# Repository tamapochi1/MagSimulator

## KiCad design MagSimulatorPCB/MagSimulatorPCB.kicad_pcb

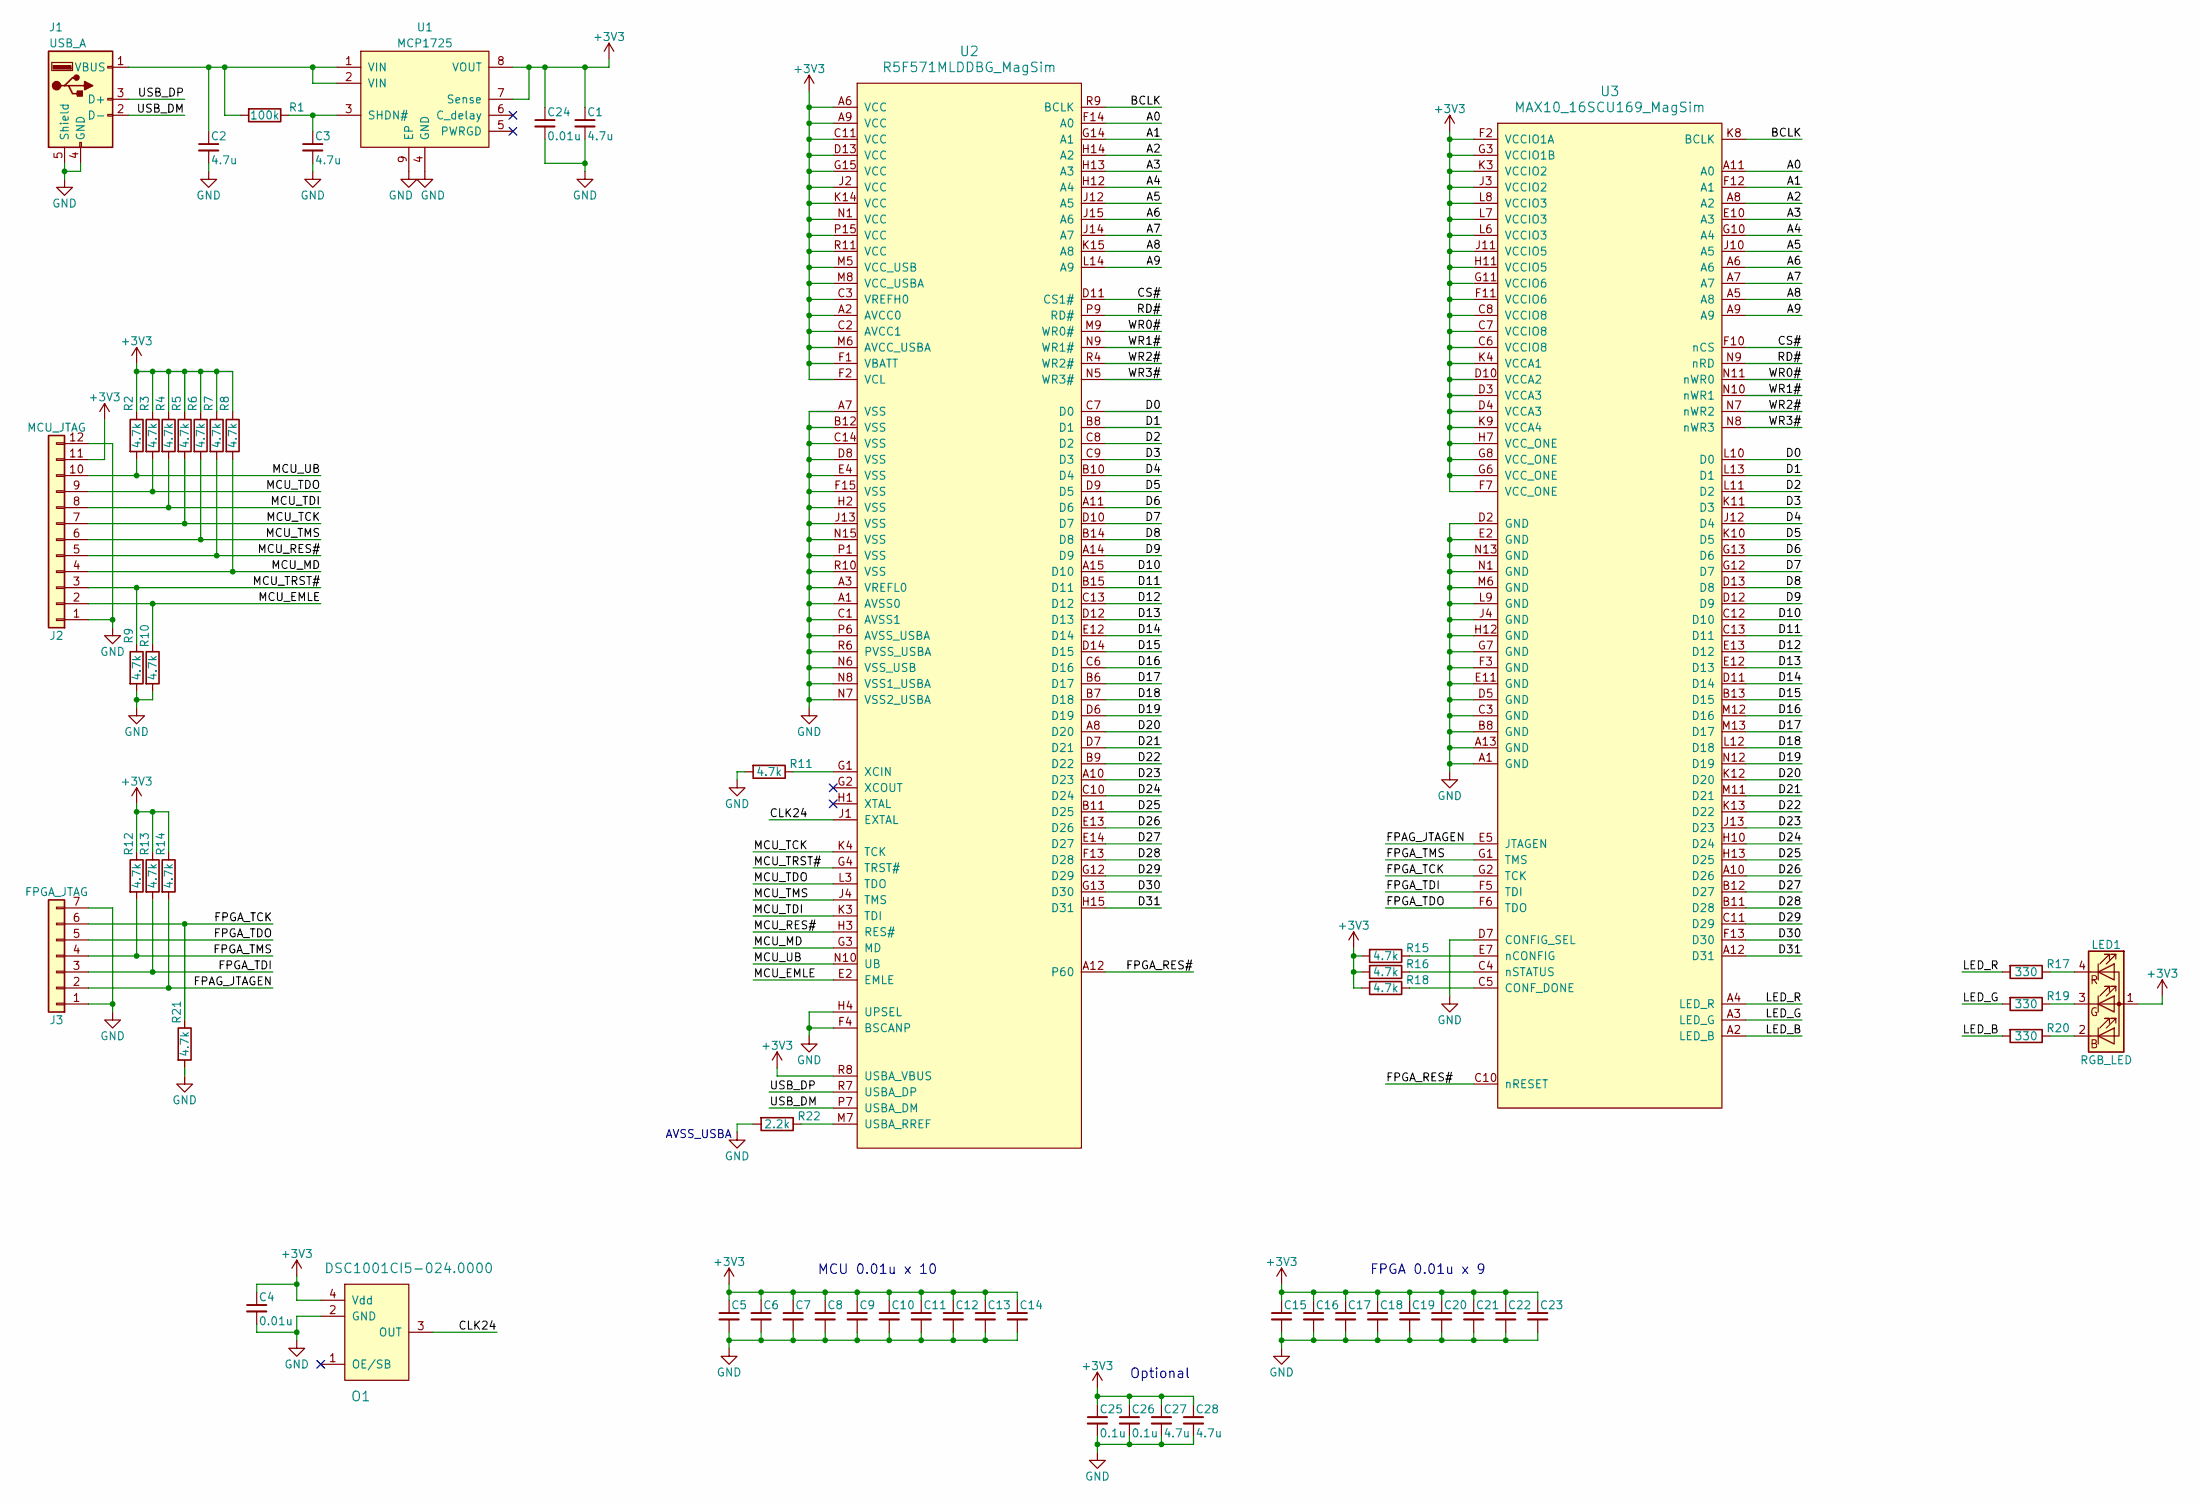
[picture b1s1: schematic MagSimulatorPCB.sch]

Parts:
C1, C2, C3, C27, C28: 4.7u; C_0402_NoSilk
C4, C5, C6, C7, C8, C9, C10, C11, C12, C13, C14, C15, C16, C17, C18, C19, C20, C21, C22, C23, C24: 0.01u; C_0402_NoSilk
C25, C26: 0.1u; C_0402_NoSilk
J1: USB_A; UP2-AH-TH
J2: MCU_JTAG; Pin_Header_Straight_1x12_Pitch1.27mm
J3: FPGA_JTAG; Pin_Header_Straight_1x07_Pitch1.27mm
LED1: RGB_LED; LED_Cree-PLCC4_2x2mm_CW
O1: DSC1001CI5-024.0000; DSC1001_CDFN-4_3.2x2.5
R1: 100k; R_0402_NoSilk
R2, R3, R4, R5, R6, R7, R8, R9, R10, R11, R12, R13, R14, R15, R16, R18, R21: 4.7k; R_0402_NoSilk
R17, R19, R20: 330; R_0402_NoSilk
R22: 2.2k; R_0402_NoSilk
U1: MCP1725; DFN-8-1EP_3x2mm_Pitch0.5mm
U2: R5F571MLDDBG_MagSim; LFBGA_176
U3: MAX10_16SCU169_MagSim; UBGA-169_A_1.55

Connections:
+3V3: C1.1, C4.1, C5.1, C6.1, C7.1, C8.1, C9.1, C10.1, C11.1, C12.1, C13.1, C14.1, C15.1, C16.1, C17.1, C18.1, C19.1, C20.1, C21.1, C22.1, C23.1, C24.1, C25.1, C26.1, C27.1, C28.1, J2.11, LED1.1 (A), O1.4 (Vdd), R2.1, R3.1, R4.1, R5.1, R6.1, R7.1, R8.1, R12.1, R13.1, R14.1, R15.2, R16.2, R18.2, U1.7 (Sense), U1.8 (VOUT), U2.A2 (AVCC0), U2.A6 (VCC), U2.A9 (VCC), U2.C2 (AVCC1), U2.C3 (VREFH0), U2.C11 (VCC), U2.D13 (VCC), U2.F1 (VBATT), U2.F2 (VCL), U2.G15 (VCC), U2.J2 (VCC), U2.K14 (VCC), U2.M5 (VCC_USB), U2.M6 (AVCC_USBA), U2.M8 (VCC_USBA), U2.N1 (VCC), U2.P15 (VCC), U2.R8 (USBA_VBUS), U2.R11 (VCC), U3.C6 (VCCIO8), U3.C7 (VCCIO8), U3.C8 (VCCIO8), U3.D3 (VCCA3), U3.D4 (VCCA3), U3.D10 (VCCA2), U3.F2 (VCCIO1A), U3.F7 (VCC_ONE), U3.F11 (VCCIO6), U3.G3 (VCCIO1B), U3.G6 (VCC_ONE), U3.G8 (VCC_ONE), U3.G11 (VCCIO6), U3.H7 (VCC_ONE), U3.H11 (VCCIO5), U3.J3 (VCCIO2), U3.J11 (VCCIO5), U3.K3 (VCCIO2), U3.K4 (VCCA1), U3.K9 (VCCA4), U3.L6 (VCCIO3), U3.L7 (VCCIO3), U3.L8 (VCCIO3)
/A0: U2.F14 (A0), U3.A11 (A0)
/A1: U2.G14 (A1), U3.F12 (A1)
/A2: U2.H14 (A2), U3.A8 (A2)
/A3: U2.H13 (A3), U3.E10 (A3)
/A4: U2.H12 (A4), U3.G10 (A4)
/A5: U2.J12 (A5), U3.J10 (A5)
/A6: U2.J15 (A6), U3.A6
/A7: U2.J14 (A7), U3.A7
/A8: U2.K15 (A8), U3.A5 (A8)
/A9: U2.L14 (A9), U3.A9
/BCLK: U2.R9 (BCLK), U3.K8 (BCLK)
/CLK24: O1.3 (OUT), U2.J1 (EXTAL)
/CS#: U2.D11 (CS1#), U3.F10 (nCS)
/D0: U2.C7 (D0), U3.L10 (D0)
/D1: U2.B8 (D1), U3.L13 (D1)
/D2: U2.C8 (D2), U3.L11 (D2)
/D3: U2.C9 (D3), U3.K11 (D3)
/D4: U2.B10 (D4), U3.J12 (D4)
/D5: U2.D9 (D5), U3.K10 (D5)
/D6: U2.A11 (D6), U3.G13 (D6)
/D7: U2.D10 (D7), U3.G12 (D7)
/D8: U2.B14 (D8), U3.D13 (D8)
/D9: U2.A14 (D9), U3.D12 (D9)
/D10: U2.A15 (D10), U3.C12 (D10)
/D11: U2.B15 (D11), U3.C13 (D11)
/D12: U2.C13 (D12), U3.E13 (D12)
/D13: U2.D12 (D13), U3.E12 (D13)
/D14: U2.E12 (D14), U3.D11 (D14)
/D15: U2.D14 (D15), U3.B13 (D15)
/D16: U2.C6 (D16), U3.M12 (D16)
/D17: U2.B6 (D17), U3.M13 (D17)
/D18: U2.B7 (D18), U3.L12 (D18)
/D19: U2.D6 (D19), U3.N12 (D19)
/D20: U2.A8 (D20), U3.K12 (D20)
/D21: U2.D7 (D21), U3.M11 (D21)
/D22: U2.B9 (D22), U3.K13 (D22)
/D23: U2.A10 (D23), U3.J13 (D23)
/D24: U2.C10 (D24), U3.H10 (D24)
/D25: U2.B11 (D25), U3.H13 (D25)
/D26: U2.E13 (D26), U3.A10 (D26)
/D27: U2.E14 (D27), U3.B12 (D27)
/D28: U2.F13 (D28), U3.B11 (D28)
/D29: U2.G12 (D29), U3.C11 (D29)
/D30: U2.G13 (D30), U3.F13 (D30)
/D31: U2.H15 (D31), U3.A12 (D31)
/FPAG_JTAGEN: J3.2, R14.2, U3.E5 (JTAGEN)
/FPGA_RES#: U2.A12 (P60), U3.C10 (nRESET)
/FPGA_TCK: J3.6, R21.1, U3.G2 (TCK)
/FPGA_TDI: J3.3, R13.2, U3.F5 (TDI)
/FPGA_TDO: J3.5, U3.F6 (TDO)
/FPGA_TMS: J3.4, R12.2, U3.G1 (TMS)
/LED_B: R20.2, U3.A2 (LED_B)
/LED_G: R19.2, U3.A3 (LED_G)
/LED_R: R17.2, U3.A4 (LED_R)
/MCU_EMLE: J2.2, R10.1, U2.E2 (EMLE)
/MCU_MD: J2.4, R8.2, U2.G3 (MD)
/MCU_RES#: J2.5, R7.2, U2.H3 (RES#)
/MCU_TCK: J2.7, R5.2, U2.K4 (TCK)
/MCU_TDI: J2.8, R4.2, U2.K3 (TDI)
/MCU_TDO: J2.9, R3.2, U2.L3 (TDO)
/MCU_TMS: J2.6, R6.2, U2.J4 (TMS)
/MCU_TRST#: J2.3, R9.1, U2.G4 (TRST#)
/MCU_UB: J2.10, R2.2, U2.N10 (UB)
/RD#: U2.P9 (RD#), U3.N9 (nRD)
/USB_DM: J1.2 (D-), U2.P7 (USBA_DM)
/USB_DP: J1.3 (D+), U2.R7 (USBA_DP)
/WR0#: U2.M9 (WR0#), U3.N11 (nWR0)
/WR1#: U2.N9 (WR1#), U3.N10 (nWR1)
/WR2#: U2.R4 (WR2#), U3.N7 (nWR2)
/WR3#: U2.N5 (WR3#), U3.N8 (nWR3)
GND: C1.2, C2.2, C3.2, C4.2, C5.2, C6.2, C7.2, C8.2, C9.2, C10.2, C11.2, C12.2, C13.2, C14.2, C15.2, C16.2, C17.2, C18.2, C19.2, C20.2, C21.2, C22.2, C23.2, C24.2, C25.2, C26.2, C27.2, C28.2, J1.4 (GND), J1.5 (Shield), J2.1, J2.12, J3.1, J3.7, O1.2 (GND), R9.2, R10.2, R11.2, R21.2, R22.2, U1.4 (GND), U1.9 (EP), U2.A1 (AVSS0), U2.A3 (VREFL0), U2.A7 (VSS), U2.B12 (VSS), U2.C1 (AVSS1), U2.C14 (VSS), U2.D8 (VSS), U2.E4 (VSS), U2.F4 (BSCANP), U2.F15 (VSS), U2.H2 (VSS), U2.H4 (UPSEL), U2.J13 (VSS), U2.N6 (VSS_USB), U2.N7 (VSS2_USBA), U2.N8 (VSS1_USBA), U2.N15 (VSS), U2.P1 (VSS), U2.P6 (AVSS_USBA), U2.R6 (PVSS_USBA), U2.R10 (VSS), U3.A1 (GND), U3.A13 (GND), U3.B8 (GND), U3.C3 (GND), U3.D2 (GND), U3.D5 (GND), U3.D7 (CONFIG_SEL), U3.E2 (GND), U3.E11 (GND), U3.F3 (GND), U3.G7 (GND), U3.H12 (GND), U3.J4 (GND), U3.L9 (GND), U3.M6 (GND), U3.N1 (GND), U3.N13 (GND)
unnamed: C2.1, J1.1 (VBUS), R1.2, U1.1 (VIN), U1.2 (VIN)
unnamed: C3.1, R1.1, U1.3 (SHDN#)
unnamed: LED1.2 (BK), R20.1
unnamed: LED1.3 (GK), R19.1
unnamed: LED1.4 (RK), R17.1
unnamed: R11.1, U2.G1 (XCIN)
unnamed: R15.1, U3.E7 (nCONFIG)
unnamed: R16.1, U3.C4 (nSTATUS)
unnamed: R18.1, U3.C5 (CONF_DONE)
unnamed: R22.1, U2.M7 (USBA_RREF)

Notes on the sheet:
AVSS_USBA
MCU 0.01u x 10
FPGA 0.01u x 9
Optional

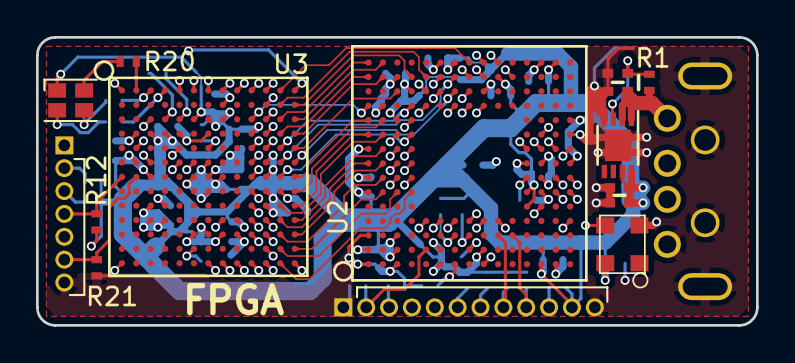
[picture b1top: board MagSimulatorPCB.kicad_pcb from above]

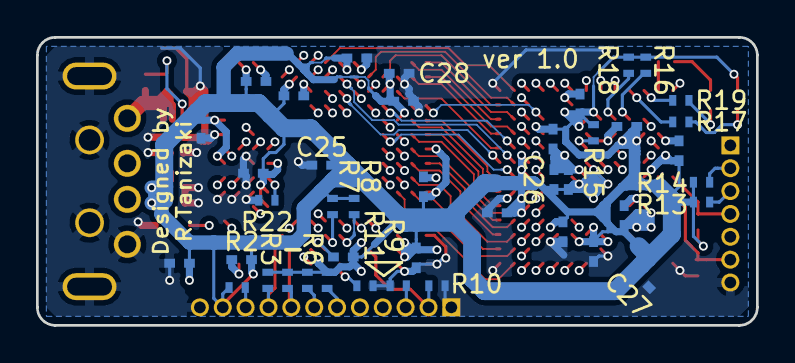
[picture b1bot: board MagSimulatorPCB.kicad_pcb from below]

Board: 4 copper layers, 40.0 x 16.0 mm, 58 parts (42 on the bottom side), 82 nets.

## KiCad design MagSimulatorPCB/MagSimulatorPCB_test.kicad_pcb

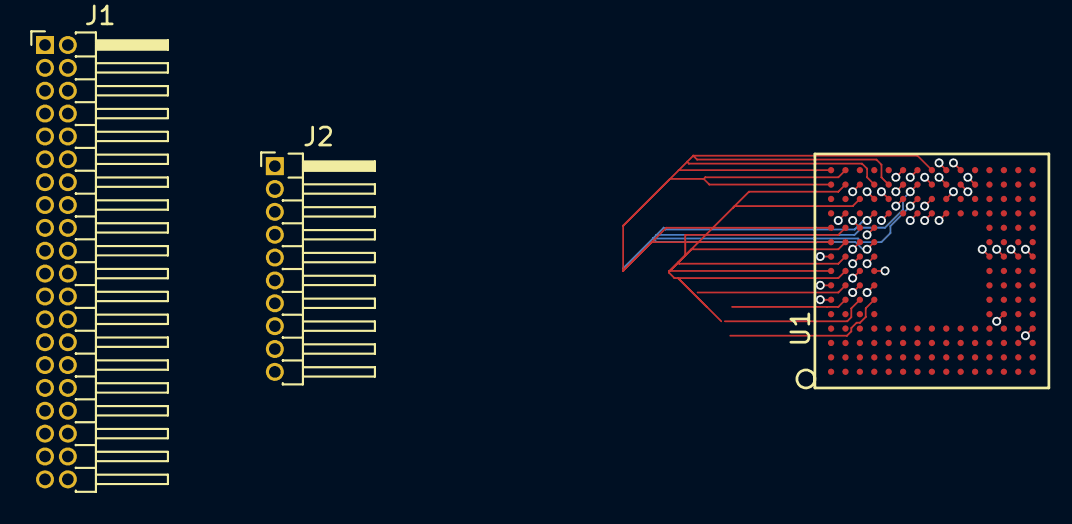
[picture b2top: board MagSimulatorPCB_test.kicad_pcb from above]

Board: 4 copper layers, 3 parts (0 on the bottom side), 51 nets.

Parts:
J1: Conn_01x40; Pin_Header_Angled_2x20_Pitch1.27mm
J2: Conn_01x10; Pin_Header_Angled_1x10_Pitch1.27mm
U1: R5F571MLDDBG_MagSim; LFBGA_176

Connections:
+3V3: U1.A2, U1.A6, U1.A9, U1.C2, U1.C3, U1.C11, U1.D13, U1.F1, U1.F2, U1.G15, U1.J2, U1.K14, U1.M5, U1.M6, U1.M8, U1.N1, U1.P15, U1.R11
/A0: J1.2, U1.F14
/A1: J1.3, U1.G14
/A2: J1.4, U1.H14
/A3: J1.5, U1.H13
/A4: J1.6, U1.H12
/A5: J1.7, U1.J12
/A6: J1.8, U1.J15
/A7: J1.9, U1.J14
/A8: J1.10, U1.K15
/A9: J1.11, U1.L14
/BCLK: J1.1, U1.R9
/CS1#: J1.13, U1.D11
/D0: J1.19, U1.C7
/D1: J1.20, U1.B8
/D2: J1.21, U1.C8
/D3: J1.22, U1.C9
/D4: J1.23, U1.B10
/D5: J1.24, U1.D9
/D6: J1.25, U1.A11
/D7: J1.26, U1.D10
/D8: J1.27, U1.B14
/D9: J1.28, U1.A14
/D10: J1.29, U1.A15
/D11: J1.30, U1.B15
/D12: J1.31, U1.C13
/D13: J1.32, U1.D12
/D14: J1.33, U1.E12
/D15: J1.34, U1.D14
/D16: J1.35, U1.C6
/D17: J1.36, U1.B6
/D18: J1.37, U1.B7
/D19: J1.38, U1.D6
/D20: J1.39, U1.A8
/D21: J1.40, U1.D7
/D22: J2.1, U1.B9
/D23: J2.2, U1.A10
/D24: J2.3, U1.C10
/D25: J2.4, U1.B11
/D26: J2.5, U1.E13
/D27: J2.6, U1.E14
/D28: J2.7, U1.F13
/D29: J2.8, U1.G12
/D30: J2.9, U1.G13
/D31: J2.10, U1.H15
/RD#: J1.14, U1.P9
/WR0#: J1.15, U1.M9
/WR1#: J1.16, U1.N9
/WR2#: J1.17, U1.R4
/WR3#: J1.18, U1.N5
GND: U1.A1, U1.A3, U1.A7, U1.B12, U1.C1, U1.C14, U1.D8, U1.E4, U1.F15, U1.H2, U1.J13, U1.N6, U1.N7, U1.N8, U1.N15, U1.P1, U1.P6, U1.R6, U1.R10

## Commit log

2018-01-11 :confetti_ball: Added .gitattributes
2018-01-11 FirstCommit
